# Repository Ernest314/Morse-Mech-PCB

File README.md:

# Morse Mech

A single-key mechanical keyboard. (Typed, of course, in [International Morse
code](1).) The software for this board can be found in [its own separate repo](2).
The following instructions may change over time, and should be taken as a guide
only. Use common sense, and feel free to submit a pull request--or even just
email me--to update this file if it gets outdated.

[1]: https://en.wikipedia.org/wiki/Morse_code
[2]: https://github.com/Ernest314/Morse-Mech-PCB

## Features

- True single-key operation
- Conforms to International Morse Code
- High-quality mechanical switch
- Adaptive signaling timing
- 16.8 million-color backlighting
- RGB indicator light
- Onboard EEPROM settings storage
- Full-speed USB operation
- USB HID-compatible device

## Version tracking

Both this repo and the [corresponding code repo](2) are pushed with the latest
updates. This means that the latest commit for this repo corresponds to the
latest commit for the code repo. If you have a legacy revision of the board,
you will either have to modify the source code (feel free to ask me for help),
or use the code repo with the closest corresponding dates.

## Assembly

The KiCAD schematic contains footprint and datasheet values for each component.
In addition to selecting components with matching values/footprints, you may
also directly use the components in the datasheets provided. When this board was
first designed, all components were available from Mouser. (The components are
very common; they will probably all be available from [Mouser](3) or [Digikey](4).
Another good resource for finding components is [Octopart](5).)

Switches and keycaps were purchased from [MAX Keyboard](6), although you can get
them from anywhere you prefer. The only limitation is that the footprint on the
PCB is that of a Cherry MX switch. (This means Gateron, Kailh, and Razer
switches should all work.)

The PCB for this board was initially manufactured by [OSH Park](7). OSH Park
accepts directly uploading `.kicad_pcb` files, and the current PCB is laid out
to the tolerances of OSHPark. Another convenient manufacturer is [DirtyPCBs](8),
although the tolerances of the board have not been tested with them. (Some
adjustments may be needed.) The PCB fits inside the 5cm x 5cm smaller limit for
PCB sizes, and is pretty close to that size.

A stencil for the board was ordered from [OSH Stencils](9). This was because I
needed additional stencils, and it was cheap enough that I decided it was worth
it to combine them and get them shipped. However, it is completely feasible to
laser-cut the stencils.

The initial run of this board did not have a case, but one can easily be created
for it. There are no mounting holes (other than the extra stabilization pins for
PCB-mounted switches). An easy way would be to 3D-print a case, or to create a
sandwiched laser-cut case. The board can be secured with hot glue, double-sided
tape, or just by sandwiching the corners of the PCB.

[3]: http://www.mouser.com/
[4]: http://www.digikey.com/
[5]: https://octopart.com/
[6]: http://www.maxkeyboard.com/
[7]: https://oshpark.com/
[8]: http://dirtypcbs.com/store/pcbs
[9]: https://www.oshstencils.com/#

## Programming

The AVR can be programmed with any AVR programmer (compatible with ATmegas). The
initial run of the boards were programmed with an Atmel-ICE programmer. (The
specific AVR that the programmer should be compatible with is the `ATmega16u2`.)
The AVR is interfaced with a standard 6-pin ICSP header, with the square pad
denoting "pad 1". The pads provided on the board are not meant to have a
shrouded header soldered on; instead, a Pogo pin <-> ICSP adapter was used to
program the AVR.

Again, the code for the board can be found in [its own repo](2). (See above
discussion of repo compatibility.) [Atmel Studio 7](10) was used to program the
board--see that repo for more details.

[10]: http://www.atmel.com/microsite/atmel-studio/

## Operating instructions

*Finally! What you were waiting for!*

As a *true* Morse code keyboard (there is **a single switch**, not two like
with many other keyboards), there is some additional setup that is needed to run
the board. For additional details (e.g. the different indicator light meanings),
reference [the code repo](2) for this board.

In order to start sending data to the computer, the keyboard needs to first be
placed into "active" mode. This consists of entering the [prosign](11) `<CT>`
(mneumonic "copy this"). Behind the scenes, this allows the microcontroller to
figure out the lengths of the operator's particular timings for dots and dashes.
Correspondingly, to suspend the keyboard, enter the prosign `<SK>` (mneumonic
"silence key").

As for entering actual characters, the keyboard accepts standard [International
Morse Code](1). This includes letters, numbers, and punctuation. There is no way
to enter lower-case letters; all letters are entered in upper-case (in authentic
telegram style). **This is a feature, not a bug.** Character and word breaks are
delimited by the standard intervals--3 and 7 times the length of a "dot",
respectively.

[11]: https://en.wikipedia.org/wiki/Prosigns_for_Morse_code

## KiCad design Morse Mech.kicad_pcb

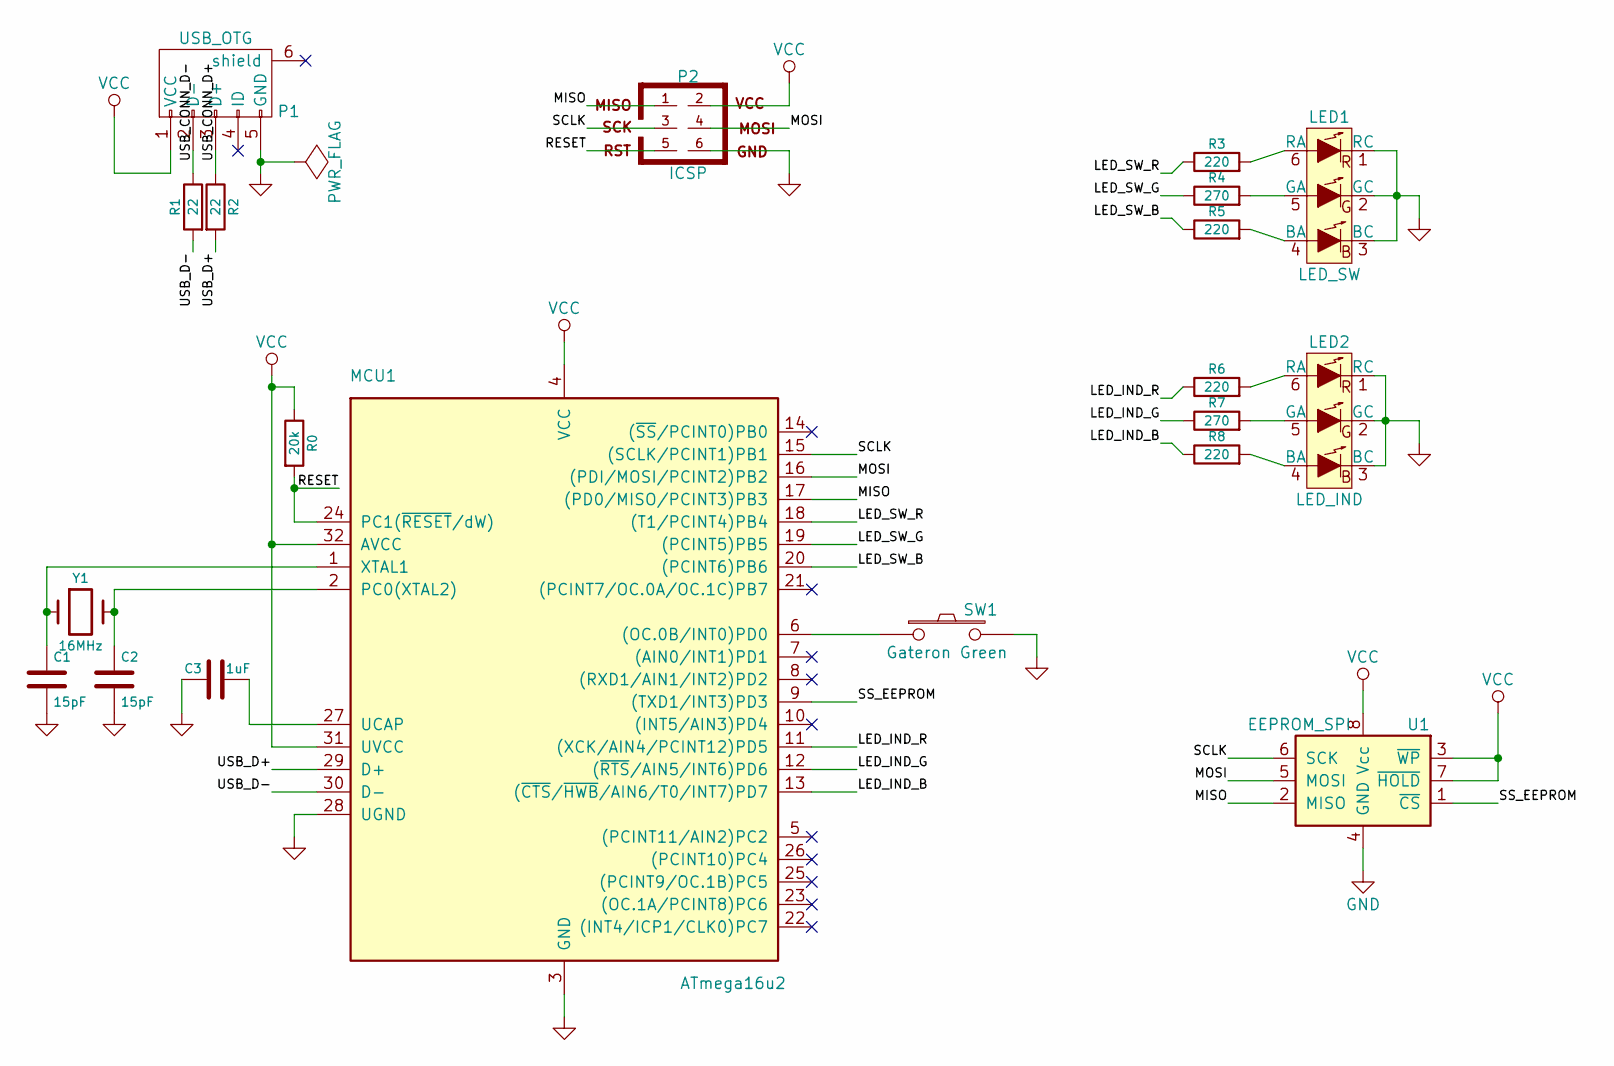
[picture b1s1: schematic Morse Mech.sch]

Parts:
C1, C2: 15pF; C_0603
C3: 1uF; C_0603
LED1: LED_SW; PLCC6_CREE
LED2: LED_IND; PLCC6_CREE
MCU1: ATmega16u2; TQFP-32_7x7mm_Pitch0.8mm
P1: USB_OTG; WURTH_USB_MICRO_B
P2: ICSP; ICSP_6PIN_POGO
R0: 20k; R_0603
R1, R2: 22; R_0603
R3, R5, R6, R8: 220; R_0603
R4, R7: 270; R_0603
SW1: Gateron Green; CHERRY_PCB_100H
U1: EEPROM_SPI; TSSOP-8_4.4x3mm_Pitch0.65mm
Y1: 16MHz; Crystal_HC49-U_Vertical

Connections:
/LED_IND_B: MCU1.13 ((~CTS~/~HWB~/AIN6/T0/INT7)PD7), R8.1
/LED_IND_G: MCU1.12 ((~RTS~/AIN5/INT6)PD6), R7.1
/LED_IND_R: MCU1.11 ((XCK/AIN4/PCINT12)PD5), R6.1
/LED_SW_B: MCU1.20 ((PCINT6)PB6), R5.1
/LED_SW_G: MCU1.19 ((PCINT5)PB5), R4.1
/LED_SW_R: MCU1.18 ((T1/PCINT4)PB4), R3.1
/MISO: MCU1.17 ((PD0/MISO/PCINT3)PB3), P2.1, U1.2 (MISO)
/MOSI: MCU1.16 ((PDI/MOSI/PCINT2)PB2), P2.4, U1.5 (MOSI)
/RESET: MCU1.24 (PC1(~RESET~/dW)), P2.5, R0.2
/SCLK: MCU1.15 ((SCLK/PCINT1)PB1), P2.3, U1.6 (SCK)
/SS_EEPROM: MCU1.9 ((TXD1/INT3)PD3), U1.1 (~CS)
/USB_CONN_D+: P1.3 (D+), R2.1
/USB_CONN_D-: P1.2 (D-), R1.1
/USB_D+: MCU1.29 (D+), R2.2
/USB_D-: MCU1.30 (D-), R1.2
GND: C1.2, C2.2, C3.1, LED1.1 (RC), LED1.2 (GC), LED1.3 (BC), LED2.1 (RC), LED2.2 (GC), LED2.3 (BC), MCU1.3 (GND), MCU1.28 (UGND), P1.5 (GND), P2.6, SW1.2, U1.4 (GND)
unnamed: C1.1, MCU1.1 (XTAL1), Y1.1
unnamed: C2.1, MCU1.2 (PC0(XTAL2)), Y1.2
unnamed: C3.2, MCU1.27 (UCAP)
unnamed: LED1.4 (BA), R5.2
unnamed: LED1.5 (GA), R4.2
unnamed: LED1.6 (RA), R3.2
unnamed: LED2.4 (BA), R8.2
unnamed: LED2.5 (GA), R7.2
unnamed: LED2.6 (RA), R6.2
unnamed: MCU1.6 ((OC.0B/INT0)PD0), SW1.1
VCC: MCU1.4 (VCC), MCU1.31 (UVCC), MCU1.32 (AVCC), P1.1 (VCC), P2.2, R0.1, U1.3 (~WP), U1.7 (~HOLD), U1.8 (Vcc)

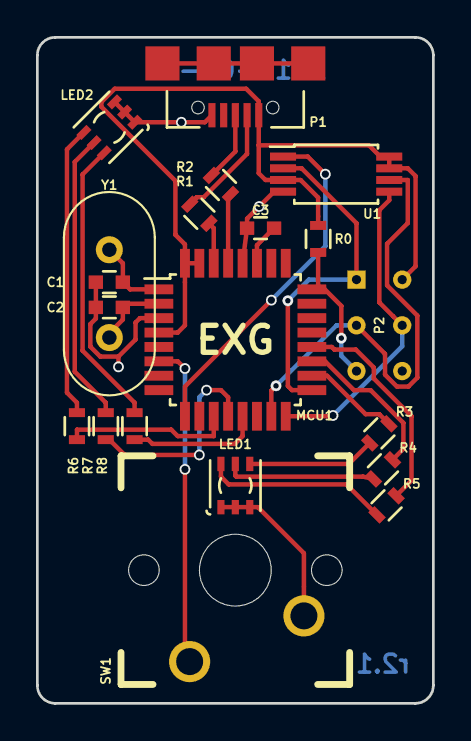
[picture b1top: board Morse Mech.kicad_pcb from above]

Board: 2 copper layers, 22.0 x 37.0 mm, 20 parts (0 on the bottom side), 27 nets.

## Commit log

2017-01-12 Added .svg files for silkscreens
    The exported .png files are ignored (can be exported from inkscape).
2017-01-12 Updated .gitignore
    - Gerbers (these count as exported files)
    - (silkscreen) images
2017-01-12 Added preference/settings files
    Syncing these since they do affect how components are added and placed.
2017-01-12 Updated .gitignore
    Now ignores autorouter import/export files.
2017-01-12 Added library cache
    According to KiCAD, allows others with missing/conflicting components to open the files. NOTE: Not sure if these actually work...
2017-01-12 Added all project files (pcb/schematics)
2017-01-12 Updated README with assumbly instructions
    (in preparation for release tagging)
2017-01-12 Added operating instructions to README
    This should be the final commit before tagging r1.6.
2017-01-12 Added feature list to README
2017-01-12 Clarified ICSP programming pads (README)
2017-01-12 Clarified how to enter spaces (README)
2017-01-13 Expanded .gitignore for PDFs
    (and slightly reformatted it)
2017-01-15 Updated schematic with PTH crystal
    Takes up less space than the SMD version, surprisingly...
    Corresponding datasheet also updated.
2017-01-15 New PCB! (r2.1)
    - More compact
    - Shorter USB data lines
    - Shorter tracks to crystal
    - Fewer vias
    - Better silkscreen
